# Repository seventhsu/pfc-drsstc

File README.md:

# pfc-drsstc
A DRSSTC with a boost-type PFC front end, all on a single circuit board.

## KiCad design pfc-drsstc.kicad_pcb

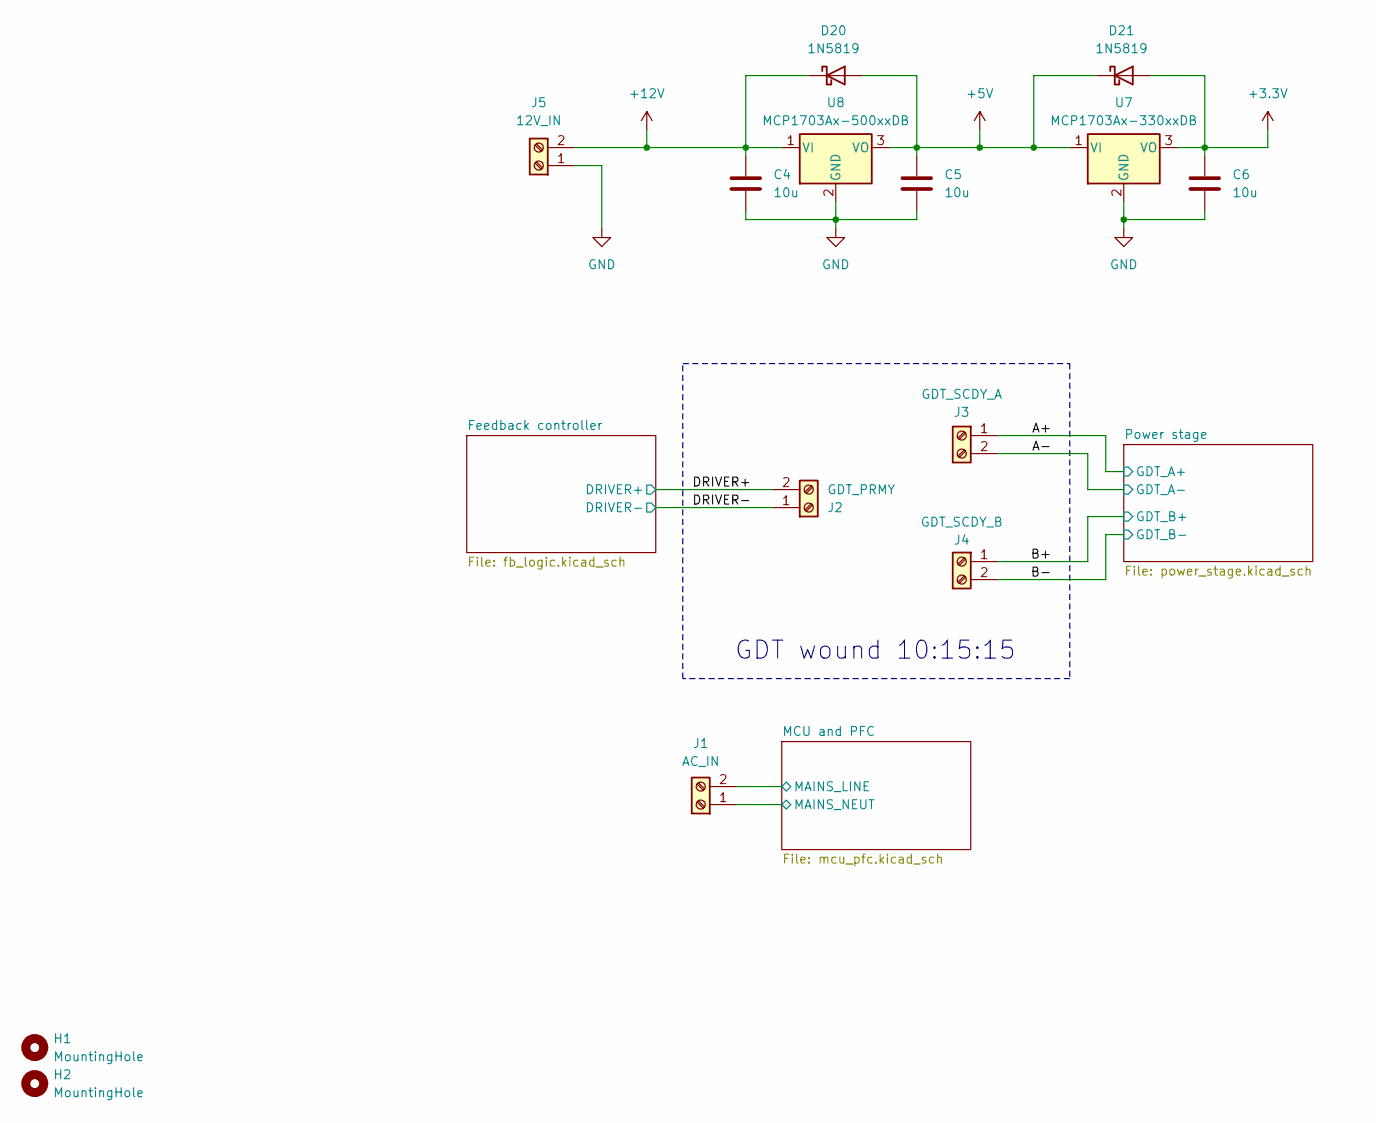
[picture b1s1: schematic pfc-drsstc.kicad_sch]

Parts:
C4, C5, C6: 10u; C_0805_2012Metric
D20, D21: 1N5819; D_DO-41_SOD81_P2.54mm_Vertical_AnodeUp
H1, H2: MountingHole; MountingHole_3.2mm_M3
J1: AC_IN; TerminalBlock_Phoenix_MKDS-1,5-2_1x02_P5.00mm_Horizontal
J2: GDT_PRMY; TerminalBlock_Phoenix_MKDS-1,5-2_1x02_P5.00mm_Horizontal
J3: GDT_SCDY_A; TerminalBlock_Phoenix_MKDS-1,5-2_1x02_P5.00mm_Horizontal
J4: GDT_SCDY_B; TerminalBlock_Phoenix_MKDS-1,5-2_1x02_P5.00mm_Horizontal
J5: 12V_IN; TerminalBlock_Phoenix_MKDS-1,5-2_1x02_P5.00mm_Horizontal
U7: MCP1703Ax-330xxDB; SOT-223-3_TabPin2
U8: MCP1703Ax-500xxDB; SOT-223-3_TabPin2

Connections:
+3.3V: C6.1, D21.2 (A), U7.3 (VO); also elsewhere on the board
+5V: C5.1, D20.2 (A), D21.1 (K), U7.1 (VI), U8.3 (VO); also elsewhere on the board
+12V: C4.1, D20.1 (K), J5.2, U8.1 (VI); also elsewhere on the board
/A+: J3.1; also elsewhere on the board
/A-: J3.2; also elsewhere on the board
/B+: J4.1; also elsewhere on the board
/DRIVER+: J2.2; also elsewhere on the board
/DRIVER-: J2.1; also elsewhere on the board
/MCU and PFC/MAINS_LINE: J1.2; also elsewhere on the board
/MCU and PFC/MAINS_NEUT: J1.1; also elsewhere on the board
GND: C4.2, C5.2, C6.2, J4.2, J5.1, U7.2 (GND), U8.2 (GND); also elsewhere on the board

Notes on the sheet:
GDT wound 10:15:15

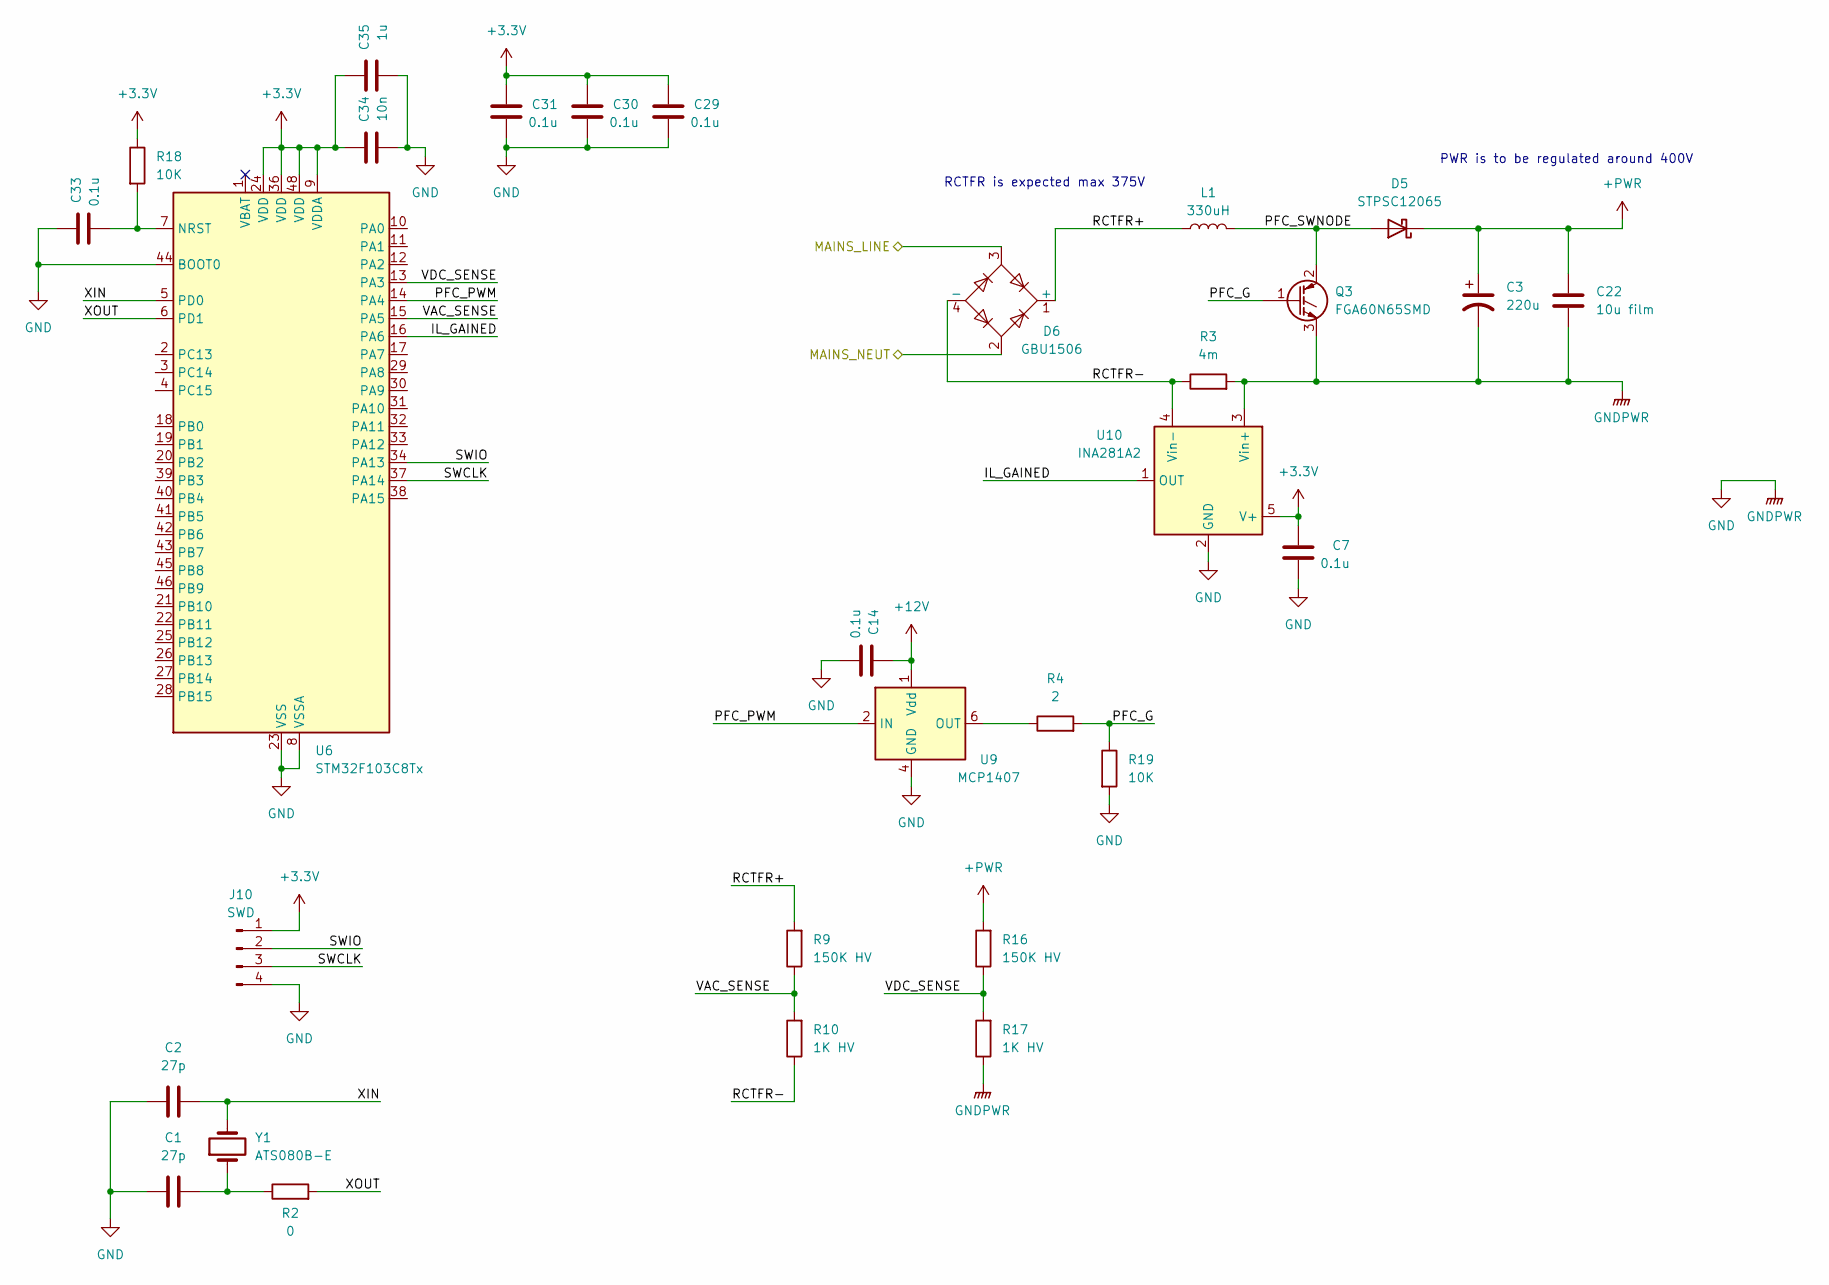
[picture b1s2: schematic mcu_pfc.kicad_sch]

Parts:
C1, C2: 27p; C_0805_2012Metric
C3: 220u; CP_Radial_D35.0mm_P10.00mm_SnapIn
C7, C14, C29, C30, C31, C33: 0.1u; C_0805_2012Metric
C22: 10u film; C_Rect_L31.5mm_W15.0mm_P27.50mm_MKS4
C34: 10n; C_0805_2012Metric
C35: 1u; C_0805_2012Metric
D5: STPSC12065; TO-220-2_Vertical
D6: GBU1506; Diode_Bridge_Vishay_GBU
J10: SWD; PinHeader_1x04_P2.54mm_Vertical
L1: 330uH; TerminalBlock_Phoenix_MKDS-1,5-2_1x02_P5.00mm_Horizontal
Q3: FGA60N65SMD; TO-3P-3_Vertical
R2: 0; R_0805_2012Metric
R3: 4m; R_2512_6332Metric
R4: 2; R_0805_2012Metric
R9, R16: 150K HV; R_1206_3216Metric
R10, R17: 1K HV; R_1206_3216Metric
R18, R19: 10K; R_0805_2012Metric
U6: STM32F103C8Tx; LQFP-48_7x7mm_P0.5mm
U9: MCP1407; SOIC-8_3.9x4.9mm_P1.27mm
U10: INA281A2; SOT-23-5
Y1: ATS080B-E; Crystal_HC49-4H_Vertical

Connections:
+3.3V: C7.2, C29.2, C30.2, C31.2, C34.2, C35.2, J10.1, R18.1, U6.9 (VDDA), U6.24 (VDD), U6.36 (VDD), U6.48 (VDD), U10.5 (V+); also elsewhere on the board
+12V: C14.2, U9.1 (Vdd), U9.8 (Vdd); also elsewhere on the board
+PWR: C3.1, C22.1, D5.1 (K), R16.2; also elsewhere on the board
/MCU and PFC/IL_GAINED: U6.16 (PA6), U10.1 (OUT)
/MCU and PFC/MAINS_LINE: D6.3; also elsewhere on the board
/MCU and PFC/MAINS_NEUT: D6.2; also elsewhere on the board
/MCU and PFC/PFC_G: Q3.1 (G), R4.2, R19.1
/MCU and PFC/PFC_PWM: U6.14 (PA4), U9.2 (IN)
/MCU and PFC/PFC_SWNODE: D5.2 (A), L1.1, Q3.2 (C)
/MCU and PFC/RCTFR+: D6.1 (+), L1.2, R9.2
/MCU and PFC/RCTFR-: D6.4 (-), R3.1, R10.1, U10.4 (Vin-)
/MCU and PFC/SWCLK: J10.3, U6.37 (PA14)
/MCU and PFC/SWIO: J10.2, U6.34 (PA13)
/MCU and PFC/VAC_SENSE: R9.1, R10.2, U6.15 (PA5)
/MCU and PFC/VDC_SENSE: R16.1, R17.2, U6.13 (PA3)
/MCU and PFC/XIN: C2.2, U6.5 (PD0), Y1.2
/MCU and PFC/XOUT: R2.2, U6.6 (PD1)
GND: C1.1, C2.1, C3.2, C7.1, C14.1, C22.2, C29.1, C30.1, C31.1, C33.2, C34.1, C35.1, J10.4, Q3.3 (E), R3.2, R17.1, R19.2, U6.8 (VSSA), U6.23 (VSS), U6.35 (VSS), U6.44 (BOOT0), U6.47 (VSS), U9.4 (GND), U9.5 (GND), U10.2 (GND), U10.3 (Vin+); also elsewhere on the board
unnamed: C1.2, R2.1, Y1.1
unnamed: R4.1, U9.6 (OUT), U9.7 (OUT)
unnamed: C33.1, R18.2, U6.7 (NRST)

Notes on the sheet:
RCTFR is expected max 375V
PWR is to be regulated around 400V

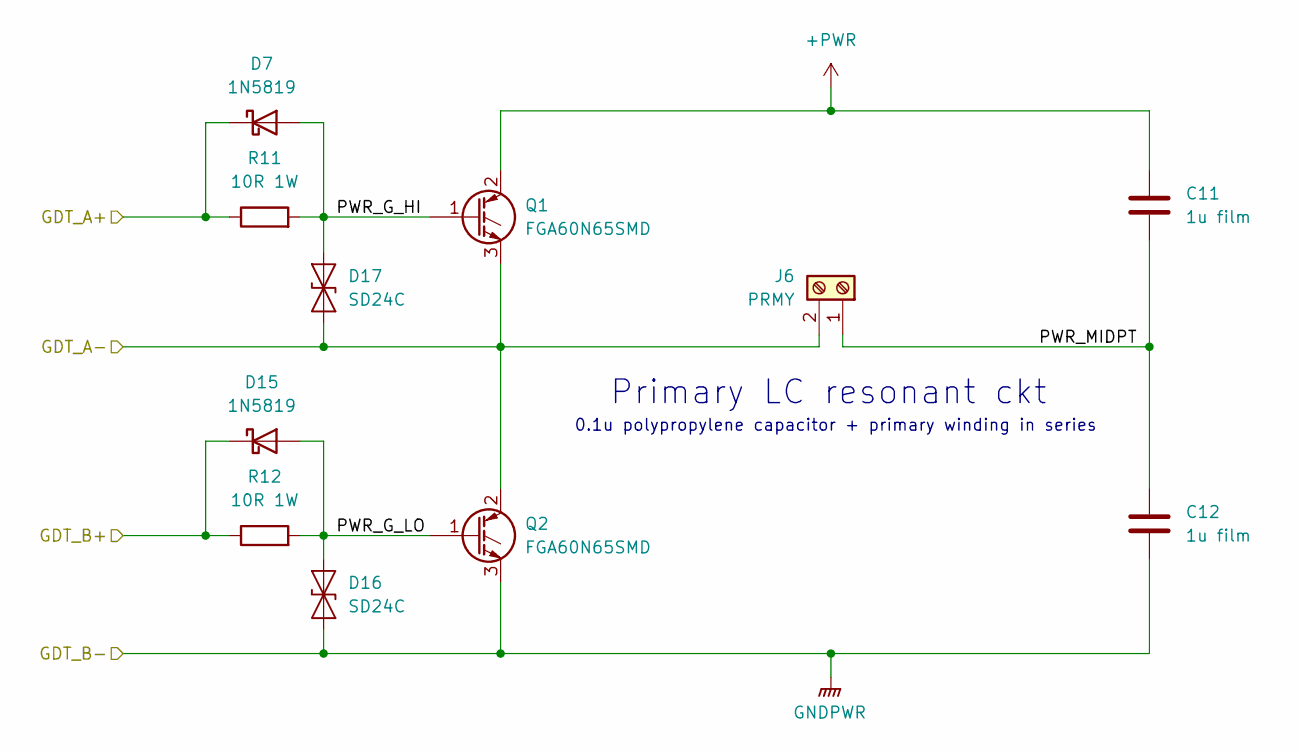
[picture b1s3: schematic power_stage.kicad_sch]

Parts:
C11, C12: 1u film; C_Rect_L26.5mm_W10.5mm_P22.50mm_MKS4
D7, D15: 1N5819; D_DO-41_SOD81_P2.54mm_Vertical_AnodeUp
D16, D17: SD24C; D_SOD-323
J6: PRMY; TerminalBlock_Phoenix_MKDS-1,5-2_1x02_P5.00mm_Horizontal
Q1, Q2: FGA60N65SMD; TO-3P-3_Vertical
R11, R12: 10R 1W; R_2512_6332Metric

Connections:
+PWR: C11.1, Q1.2 (C); also elsewhere on the board
/A+: D7.1 (K), R11.1; also elsewhere on the board
/A-: D17.1 (A1), J6.2, Q1.3 (E), Q2.2 (C); also elsewhere on the board
/B+: D15.1 (K), R12.1; also elsewhere on the board
/Power stage/PWR_G_HI: D7.2 (A), D17.2 (A2), Q1.1 (G), R11.2
/Power stage/PWR_G_LO: D15.2 (A), D16.2 (A2), Q2.1 (G), R12.2
/Power stage/PWR_MIDPT: C11.2, C12.1, J6.1
GND: C12.2, D16.1 (A1), Q2.3 (E); also elsewhere on the board

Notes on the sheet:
Primary LC resonant ckt
0.1u polypropylene capacitor + primary winding in series

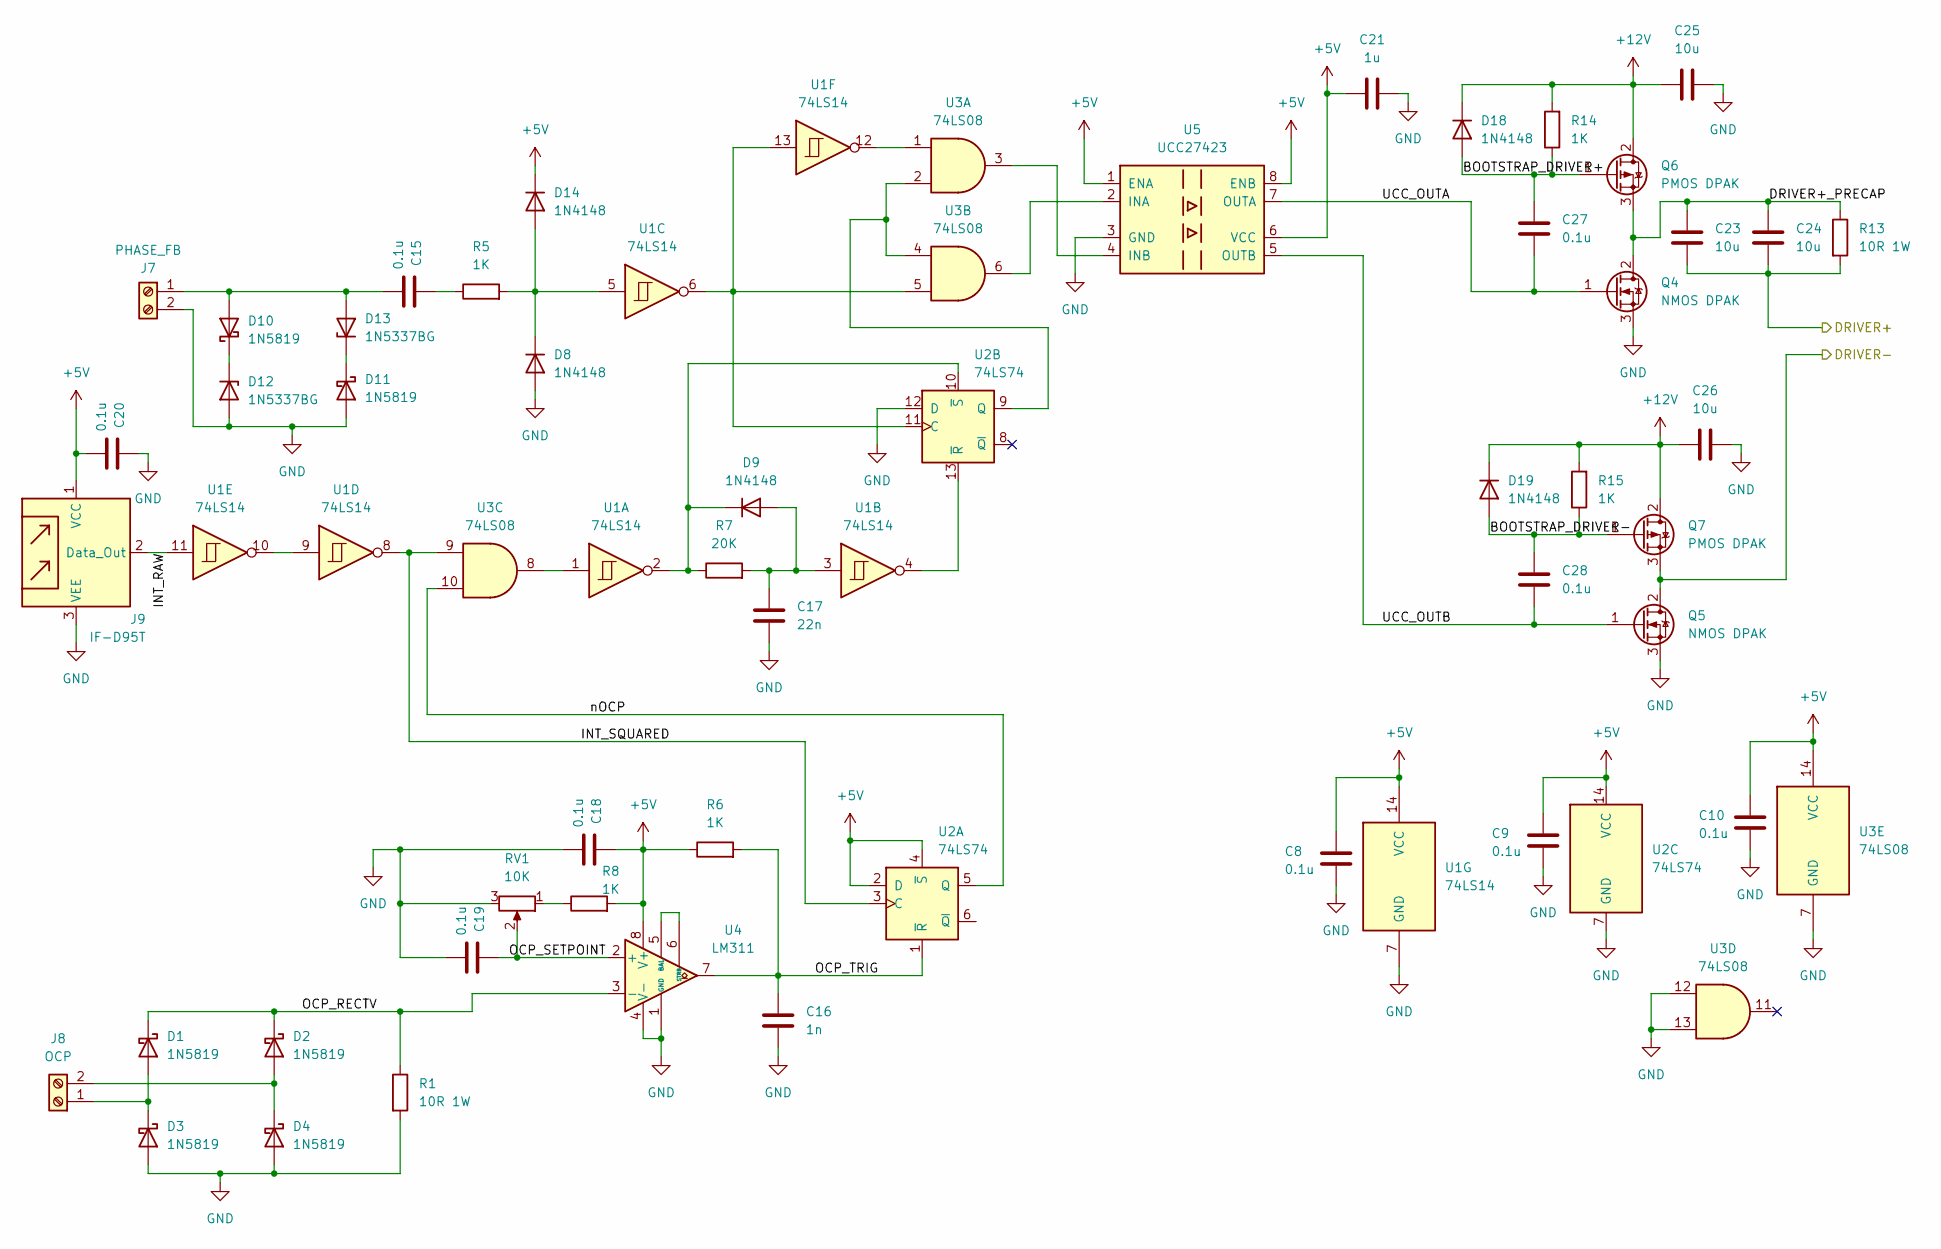
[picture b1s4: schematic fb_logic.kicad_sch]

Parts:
C8, C9, C10, C15, C18, C19, C20, C27, C28: 0.1u; C_0805_2012Metric
C16: 1n; C_0805_2012Metric
C17: 22n; C_0805_2012Metric
C21: 1u; C_0805_2012Metric
C23, C24, C25, C26: 10u; C_1206_3216Metric
D1, D2, D3, D4, D10, D11: 1N5819; D_DO-41_SOD81_P2.54mm_Vertical_AnodeUp
D8, D9, D14, D18, D19: 1N4148; D_DO-35_SOD27_P2.54mm_Vertical_AnodeUp
D12, D13: 1N5337BG; D_5KPW_P7.62mm_Vertical_AnodeUp
J7: PHASE_FB; TerminalBlock_Phoenix_MKDS-1,5-2_1x02_P5.00mm_Horizontal
J8: OCP; TerminalBlock_Phoenix_MKDS-1,5-2_1x02_P5.00mm_Horizontal
J9: IF-D95T; TO-92_Inline_Wide
Q4, Q5: NMOS DPAK; TO-252-2
Q6, Q7: PMOS DPAK; TO-252-2
R1, R13: 10R 1W; R_2512_6332Metric
R5, R6, R8, R14, R15: 1K; R_0805_2012Metric
R7: 20K; R_0805_2012Metric
RV1: 10K; Potentiometer_Bourns_3386P_Vertical
U1: 74LS14; SOIC-14_3.9x8.7mm_P1.27mm
U2: 74LS74; SOIC-14_3.9x8.7mm_P1.27mm
U3: 74LS08; SOIC-14_3.9x8.7mm_P1.27mm
U4: LM311; SOIC-8_3.9x4.9mm_P1.27mm
U5: UCC27423; SOIC-8_3.9x4.9mm_P1.27mm

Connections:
+5V: C8.2, C9.2, C10.2, C18.2, C20.1, C21.1, D14.1 (K), J9.1 (VCC), R6.1, R8.2, U1.14 (VCC), U2.2 (D), U2.4 (~S), U2.14 (VCC), U3.14 (VCC), U4.8 (V+), U5.1 (ENA), U5.6 (VCC), U5.8 (ENB); also elsewhere on the board
+12V: C25.1, C26.1, D18.1 (K), D19.1 (K), Q6.2 (D), Q7.2 (D), R14.2, R15.2; also elsewhere on the board
/DRIVER+: C23.2, C24.2, R13.2; also elsewhere on the board
/DRIVER-: Q5.2 (D), Q7.3 (S); also elsewhere on the board
/Feedback controller/BOOTSTRAP_DRIVER+: C27.2, D18.2 (A), Q6.1 (G), R14.1
/Feedback controller/BOOTSTRAP_DRIVER-: C28.2, D19.2 (A), Q7.1 (G), R15.1
/Feedback controller/DRIVER+_PRECAP: C23.1, C24.1, Q4.2 (D), Q6.3 (S), R13.1
/Feedback controller/INT_RAW: J9.2 (Data_Out), U1.11
/Feedback controller/INT_SQUARED: U1.8, U2.3 (C), U3.9
/Feedback controller/OCP_RECTV: D1.1 (K), D2.1 (K), R1.1, U4.3 (-)
/Feedback controller/OCP_SETPOINT: C19.2, RV1.2, U4.2 (+)
/Feedback controller/OCP_TRIG: C16.1, R6.2, U2.1 (~R), U4.7
/Feedback controller/UCC_OUTA: C27.1, Q4.1 (G), U5.7 (OUTA)
/Feedback controller/UCC_OUTB: C28.1, Q5.1 (G), U5.5 (OUTB)
/Feedback controller/nOCP: U2.5 (Q), U3.10
GND: C8.1, C9.1, C10.1, C16.2, C17.2, C18.1, C19.1, C20.2, C21.2, C25.2, C26.2, D3.2 (A), D4.2 (A), D8.2 (A), D11.2 (A), D12.2 (A), J7.2, J9.3 (VEE), Q4.3 (S), Q5.3 (S), R1.2, RV1.3, U1.7 (GND), U2.7 (GND), U2.12 (D), U3.7 (GND), U3.12, U3.13, U4.1 (GND), U4.4 (V-), U5.3 (GND); also elsewhere on the board
unnamed: C15.2, R5.1
unnamed: D1.2 (A), D3.1 (K), J8.1
unnamed: D2.2 (A), D4.1 (K), J8.2
unnamed: C17.1, D9.2 (A), R7.2, U1.3
unnamed: D9.1 (K), R7.1, U1.2, U2.10 (~S)
unnamed: C15.1, D10.2 (A), D13.2 (A), J7.1
unnamed: D10.1 (K), D12.1 (K)
unnamed: D11.1 (K), D13.1 (K)
unnamed: D8.1 (K), D14.2 (A), R5.2, U1.5
unnamed: R8.1, RV1.1
unnamed: U1.1, U3.8
unnamed: U1.9, U1.10
unnamed: U1.12, U3.1
unnamed: U1.6, U1.13, U2.11 (C), U3.5
unnamed: U2.9 (Q), U3.2, U3.4
unnamed: U1.4, U2.13 (~R)
unnamed: U4.5 (BAL), U4.6 (STRB)
unnamed: U3.6, U5.2 (INA)
unnamed: U3.3, U5.4 (INB)

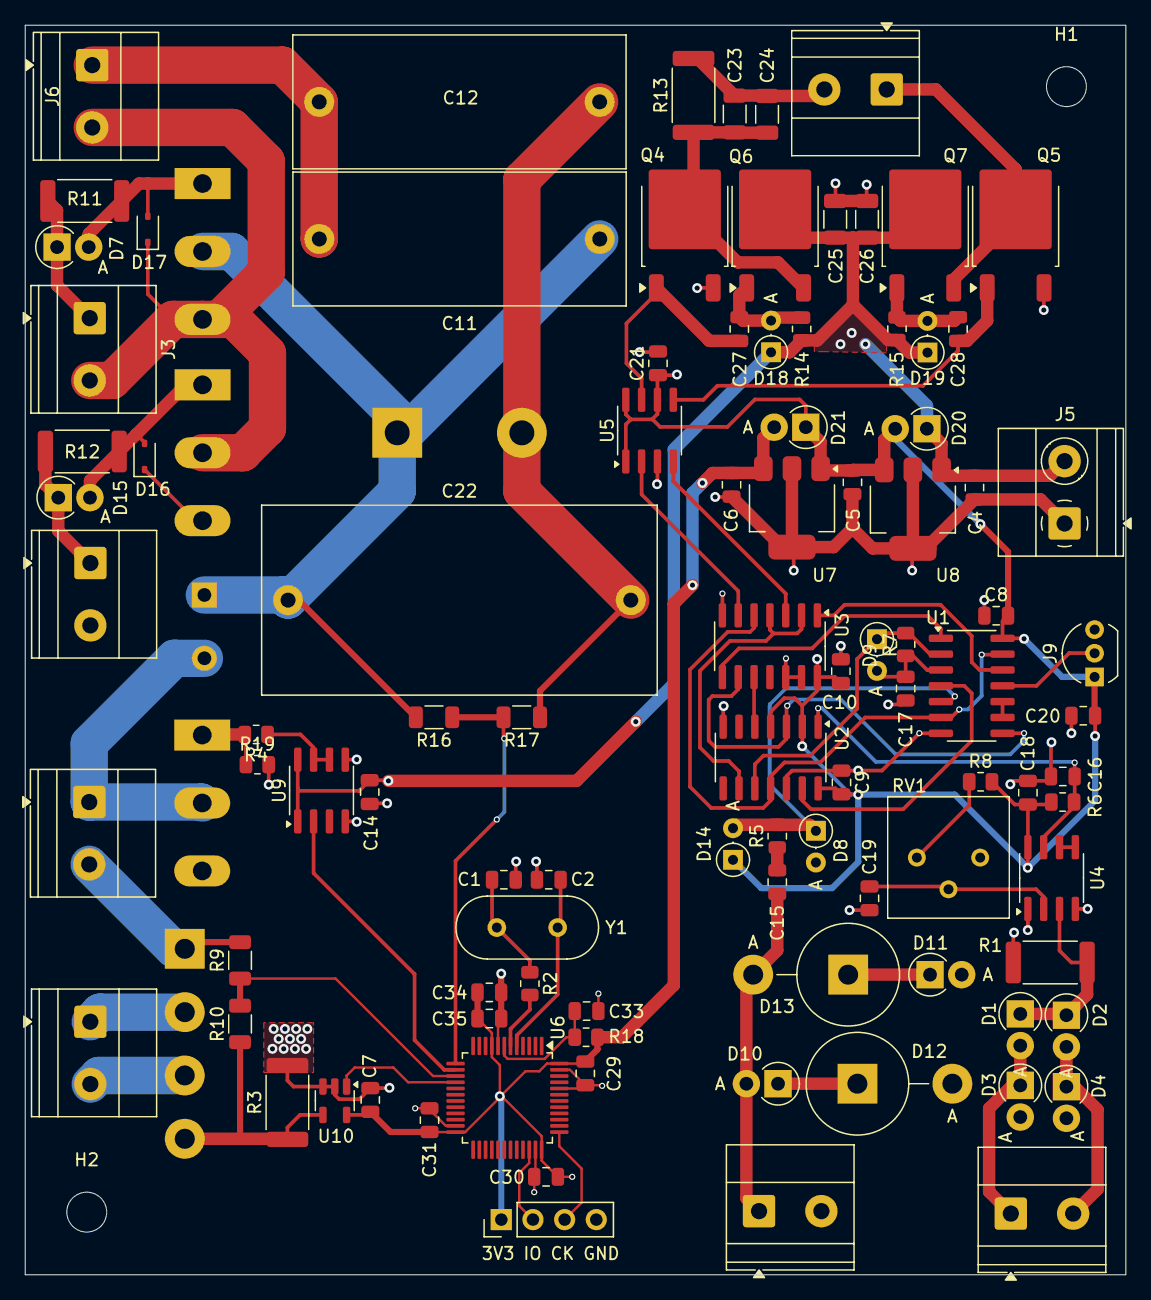
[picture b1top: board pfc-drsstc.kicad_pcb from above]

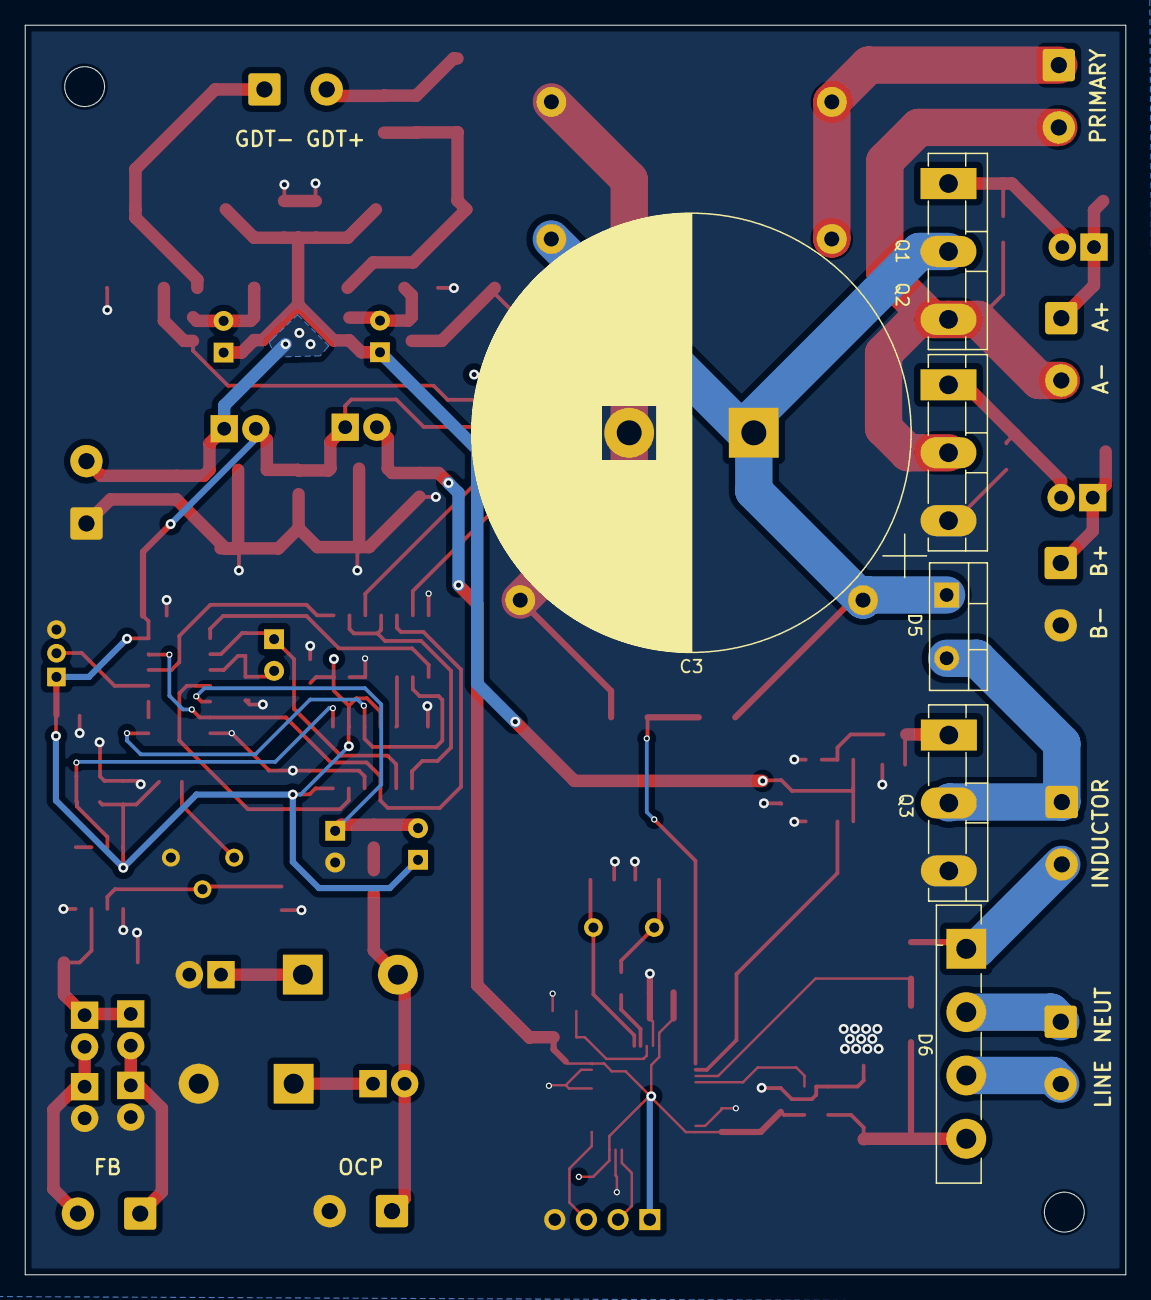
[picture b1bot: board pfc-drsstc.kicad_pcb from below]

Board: 2 copper layers, 88.3 x 100.2 mm, 105 parts (6 on the bottom side), 60 nets.

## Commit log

2025-04-07 added progress
2025-04-10 large amount of work
2025-04-10 tentative layout completion
2025-04-10 layout nearly complete
2025-04-19 Completed layout v1
